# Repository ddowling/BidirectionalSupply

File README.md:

This is a design for a Bidirectional Buck-Boost DC-DC converter based on the Texas Instruments [BQ25758](https://www.ti.com/lit/ds/symlink/bq25758.pdf) integrated circuit. 
The BQ25758 has a wide supply range from 4.2V to 60V and the external MOSFETs and Inductor should support currents up to 10A. This design is closely based on the 
[BQ25758 Evaluation Module](https://www.ti.com/lit/ug/sluucd0b/sluucd0b.pdf?ts=1762398106820&ref_url=https%253A%252F%252Fwww.ti.com%252Ftool%252FBQ25758EVM). I decided to spin my own board as I
wanted to add a microcontroller and four Ideal Diodes with load switches to make a completely standalone board. 

I am interested in using this circuit as a DC UPS, Battery Charger and Solar MPPT. I have used various purpose build modules previously but I have often run into limitations due to their fixed 
function design and closed firmware.

The BQ25758 I<sub>2</sub>C interface is connected to an on-board RP2350 and there are 4 Ideal-Diode switches also connected to the RB2350. All of the high current connections are brought out to
pluggable terminal blocks so it is possible to reconfigure the circuit to accomodate different use cases. 
Having the ability to switch the DC-DC converter direction means that the system bus voltage can be decoupled from the battery voltage.

I was originally going to use a STM32 for the board microcontroller as I have used these on a lot of previous designed but when I started looking at battery capacity tracking algorithms I noted
that the more advanced employed an Unsented Kalman Filter and required the use of an Equivalent Circuit Model for the battery. I decided to opt for the
[RP2350](https://pip-assets.raspberrypi.com/categories/1214-rp2350/documents/RP-008373-DS-2-rp2350-datasheet.pdf?disposition=inline) with its hardware floating point and
the ability to run MicroPython as I figure this will be easier to iterate the firmware and run experiments on the board. Using MicroPython allow writing log files to the flash memory to
allow continous logging of battery voltage, current and temperature. This data can then be processed either on the board or remotely to allow a battery model to be fitted to actual
battery performance.

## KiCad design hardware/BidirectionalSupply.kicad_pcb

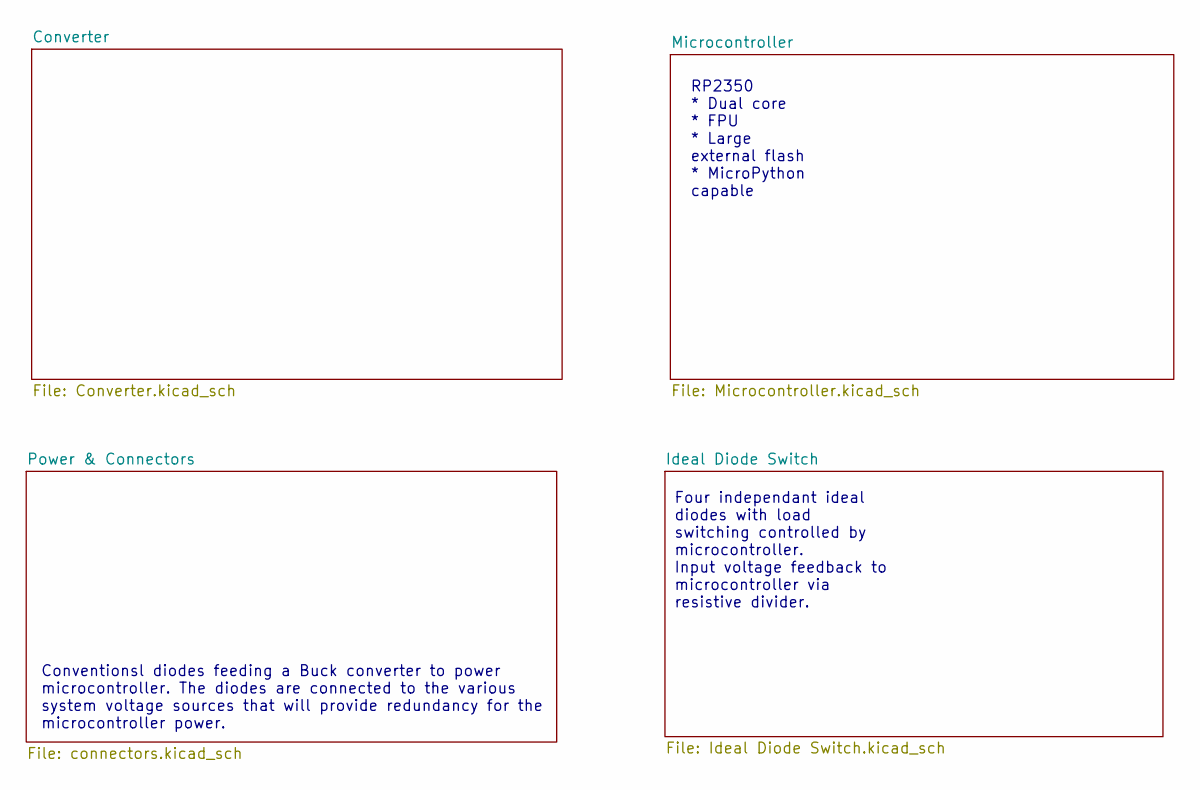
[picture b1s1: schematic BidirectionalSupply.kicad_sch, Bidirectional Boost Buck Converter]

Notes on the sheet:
RP2350 * Dual core * FPU * Large external flash * MicroPython capable
Four independant ideal diodes with load switching controlled by microcontroller. Input voltage feedback to microcontroller via resistive divider.
Conventionsl diodes feeding a Buck converter to power microcontroller. The diodes are connected to the various system voltage sources that will provide redundancy for the microcontroller power.

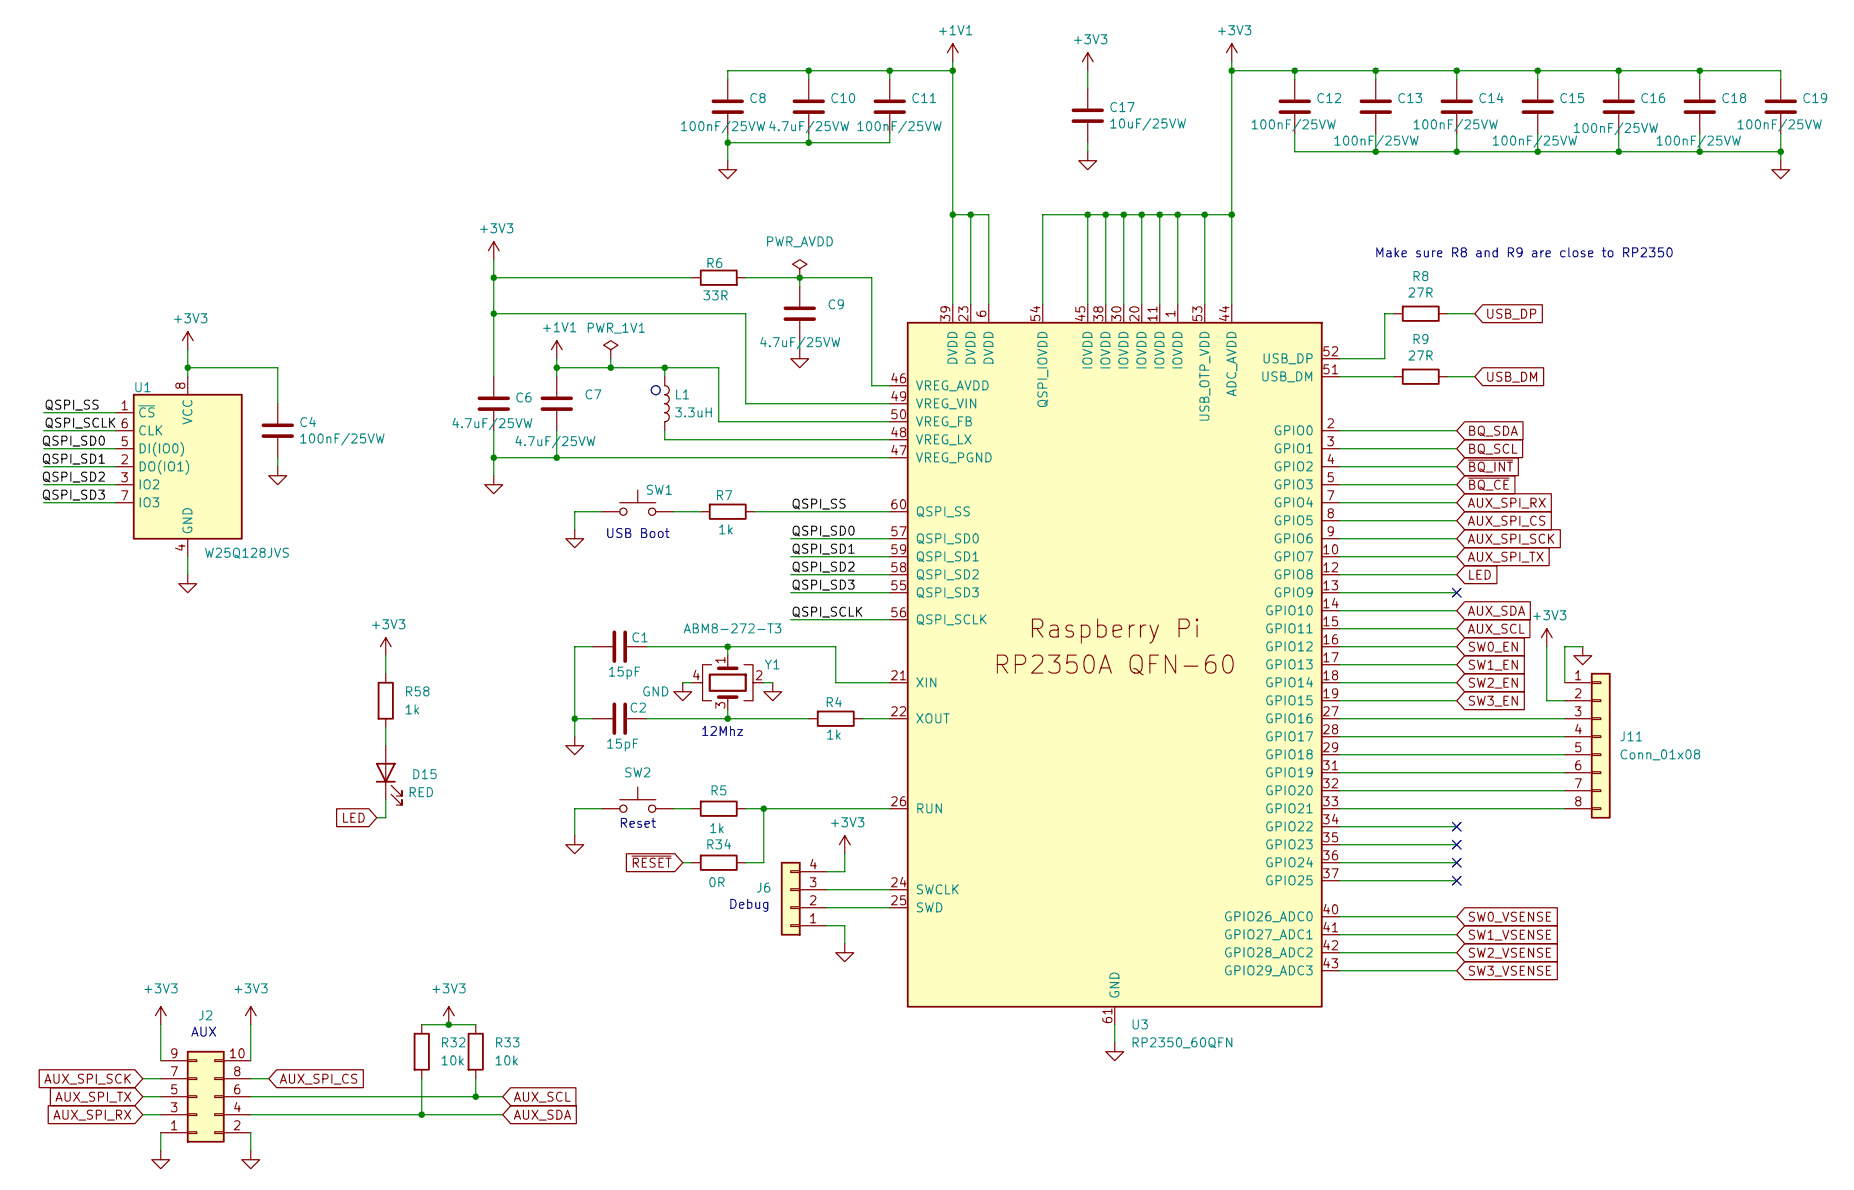
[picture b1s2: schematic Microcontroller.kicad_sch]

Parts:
C1, C2: 15pF; C_0402_DRC; JLCPCB C1548
C4, C8, C11, C12, C13, C14, C15, C16, C18, C19: 100nF/25VW; C_0603_1608Metric; JLCPCB C1590
C6, C7, C9, C10: 4.7uF/25VW; C_0805_2012Metric; JLCPCB C1779
C17: 10uF/25VW; C_0805_2012Metric; JLCPCB C15850
D15: RED; LED_0603_1608Metric; JLCPCB C2286
J2: CON10; PinHeader_2x05_P2.54mm_Vertical
J6: CON4; PinHeader_1x04_P2.54mm_Vertical
J11: Conn_01x08; PinHeader_1x08_P2.54mm_Vertical
L1: 3.3uH; L_pol_2016; JLCPCB C42411119
R4, R5, R7, R58: 1k; R_0603_1608Metric; JLCPCB C21190
R6: 33R; R_0603_1608Metric; JLCPCB C23140
R8, R9: 27R; R_0603_1608Metric; JLCPCB C25190
R32, R33: 10k; R_0603_1608Metric; JLCPCB C25804
R34: 0R; R_0603_1608Metric; JLCPCB C21189
SW1, SW2: SW_Push; TS-1088-AR02016; JLCPCB C720477
U1: W25Q128JVS; SOIC-8_5.23x5.23mm_P1.27mm; JLCPCB C97521
U3: RP2350_60QFN; RP2350-QFN-60-1EP_7x7_P0.4mm_EP3.4x3.4mm_ThermalVias; JLCPCB C42411118
Y1: ABM8-272-T3; Crystal_SMD_3225-4Pin_DRC; JLCPCB C20625731

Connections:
+1V1: C7.1, C8.1, C10.1, C11.1, L1.1, U3.6 (DVDD), U3.23 (DVDD), U3.39 (DVDD), U3.50 (VREG_FB)
+3V3: C4.1, C6.1, C12.1, C13.1, C14.1, C15.1, C16.1, C17.1, C18.1, C19.1, J2.9, J2.10, J6.4, J11.2, R6.1, R32.1, R33.1, R58.1, U1.8 (VCC), U3.1 (IOVDD), U3.11 (IOVDD), U3.20 (IOVDD), U3.30 (IOVDD), U3.38 (IOVDD), U3.44 (ADC_AVDD), U3.45 (IOVDD), U3.49 (VREG_VIN), U3.53 (USB_OTP_VDD), U3.54 (QSPI_IOVDD); also elsewhere on the board
/Microcontroller/QSPI_SCLK: U1.6 (CLK), U3.56 (QSPI_SCLK)
/Microcontroller/QSPI_SD0: U1.5 (DI(IO0)), U3.57 (QSPI_SD0)
/Microcontroller/QSPI_SD1: U1.2 (DO(IO1)), U3.59 (QSPI_SD1)
/Microcontroller/QSPI_SD2: U1.3 (IO2), U3.58 (QSPI_SD2)
/Microcontroller/QSPI_SD3: U1.7 (IO3), U3.55 (QSPI_SD3)
/Microcontroller/QSPI_SS: R7.1, U1.1 (~CS), U3.60 (QSPI_SS)
AUX_SCL: J2.6, R33.2, U3.15 (GPIO11)
AUX_SDA: J2.4, R32.2, U3.14 (GPIO10)
AUX_SPI_CS: J2.8, U3.8 (GPIO5)
AUX_SPI_RX: J2.3, U3.7 (GPIO4)
AUX_SPI_SCK: J2.7, U3.9 (GPIO6)
AUX_SPI_TX: J2.5, U3.10 (GPIO7)
BQ_SCL: U3.3 (GPIO1); also elsewhere on the board
BQ_SDA: U3.2 (GPIO0); also elsewhere on the board
GND: C1.2, C2.2, C4.2, C6.2, C7.2, C8.2, C9.2, C10.2, C11.2, C12.2, C13.2, C14.2, C15.2, C16.2, C17.2, C18.2, C19.2, J2.1, J2.2, J6.1, J11.1, SW1.1, SW2.1, U1.4 (GND), U3.47 (VREG_PGND), U3.61 (GND), Y1.2, Y1.4; also elsewhere on the board
LED: D15.1 (K), U3.12 (GPIO8)
unnamed: C2.1, R4.2, Y1.3
unnamed: D15.2 (A), R58.2
unnamed: J6.2, U3.25 (SWD)
unnamed: J6.3, U3.24 (SWCLK)
unnamed: J11.3, U3.27 (GPIO16)
unnamed: J11.4, U3.28 (GPIO17)
unnamed: J11.5, U3.29 (GPIO18)
unnamed: J11.6, U3.31 (GPIO19)
unnamed: J11.7, U3.32 (GPIO20)
unnamed: J11.8, U3.33 (GPIO21)
unnamed: R5.2, SW2.2
unnamed: R7.2, SW1.2
unnamed: R5.1, R34.1, U3.26 (RUN)
unnamed: R9.2, U3.51 (USB_DM)
unnamed: R8.2, U3.52 (USB_DP)
unnamed: C9.1, R6.2, U3.46 (VREG_AVDD)
unnamed: L1.2, U3.48 (VREG_LX)
unnamed: C1.1, U3.21 (XIN), Y1.1
unnamed: R4.1, U3.22 (XOUT)
SW0_EN: U3.16 (GPIO12); also elsewhere on the board
SW0_VSENSE: U3.40 (GPIO26_ADC0); also elsewhere on the board
SW1_EN: U3.17 (GPIO13); also elsewhere on the board
SW1_VSENSE: U3.41 (GPIO27_ADC1); also elsewhere on the board
SW2_EN: U3.18 (GPIO14); also elsewhere on the board
SW2_VSENSE: U3.42 (GPIO28_ADC2); also elsewhere on the board
SW3_EN: U3.19 (GPIO15); also elsewhere on the board
SW3_VSENSE: U3.43 (GPIO29_ADC3); also elsewhere on the board
USB_DM: R9.1; also elsewhere on the board
USB_DP: R8.1; also elsewhere on the board
~BQ_CE: U3.5 (GPIO3); also elsewhere on the board
~BQ_INT: U3.4 (GPIO2); also elsewhere on the board
~RESET: R34.2; also elsewhere on the board

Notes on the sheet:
Debug
Make sure R8 and R9 are close to RP2350
USB Boot
AUX
Reset
12Mhz

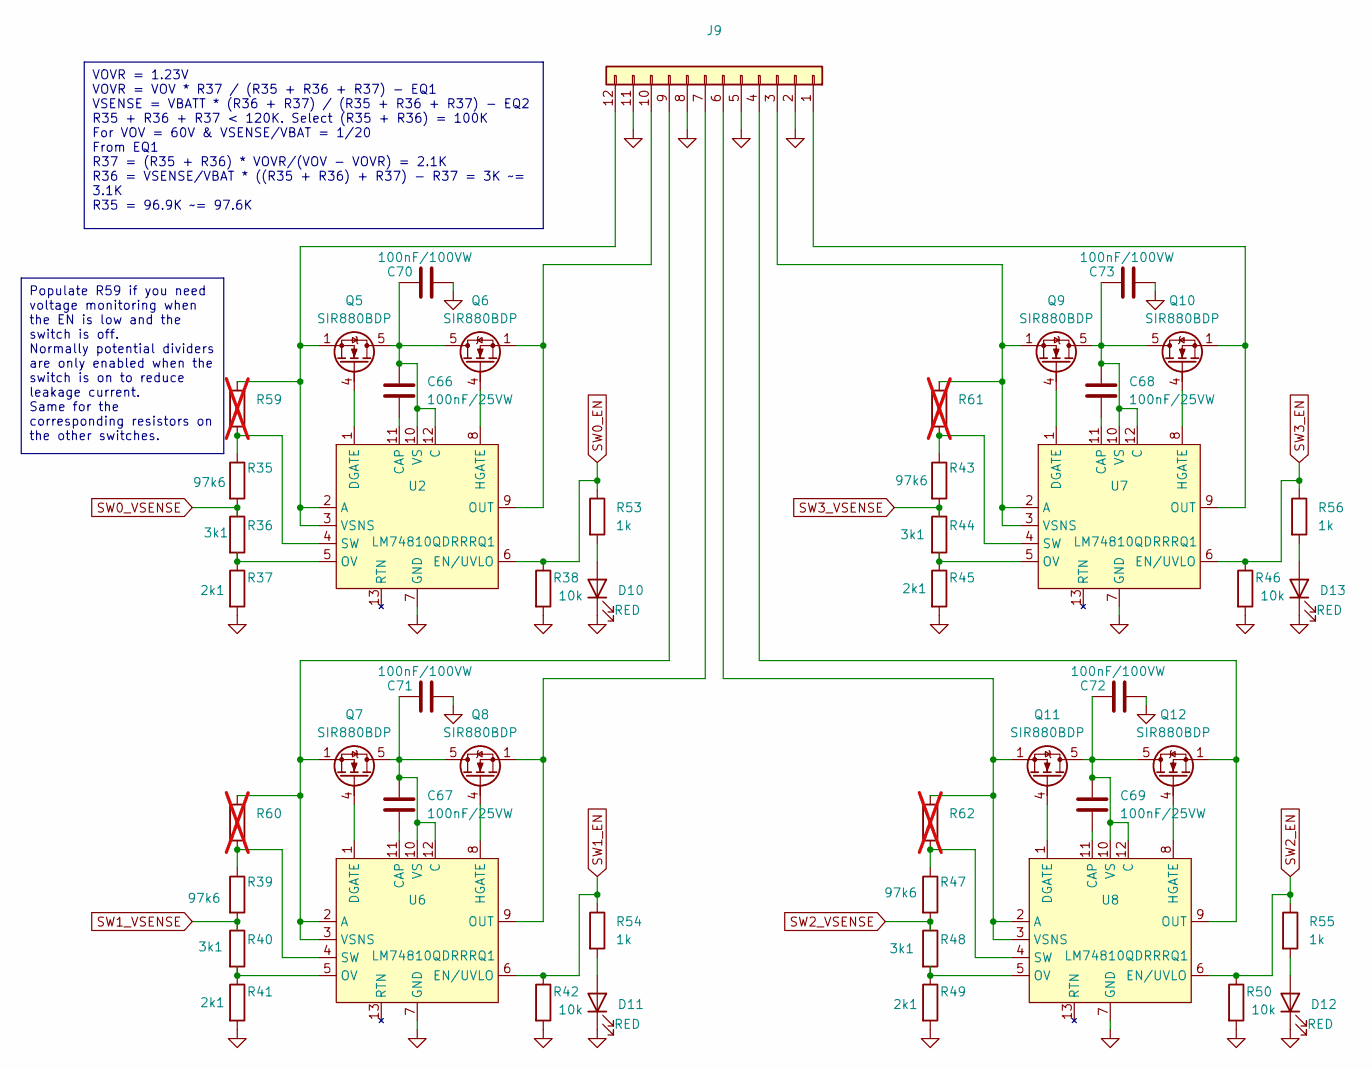
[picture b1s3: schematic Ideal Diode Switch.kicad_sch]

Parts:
C66, C67, C68, C69: 100nF/25VW; C_0603_1608Metric; JLCPCB C1590
C70, C71, C72, C73: 100nF/100VW; C_1206_3216Metric; JLCPCB C1945
D10, D11, D12, D13: RED; LED_0603_1608Metric; JLCPCB C2286
J9: Conn_01x12; PhoenixContact_MSTBVA_2,5_12-G-5,08_1x12_P5.08mm_Vertical; Mouser 651-1755833
Q5, Q6, Q7, Q8, Q9, Q10, Q11, Q12: SIR880BDP; POWERPAK-SO-8_L6.2-W5.2-P1.27-BL-EP; LCSC Part C5900133
R35, R39, R43, R47: 97k6; R_0603_1608Metric; JLCPCB C2907079
R36, R40, R44, R48: 3k1; R_0603_1608Metric; JLCPCB C2924132
R37, R41, R45, R49: 2k1; R_0603_1608Metric; JLCPCB C22902
R38, R42, R46, R50: 10k; R_0603_1608Metric; JLCPCB C25804
R53, R54, R55, R56: 1k; R_0603_1608Metric; JLCPCB C21190
R59, R60, R61, R62: 0R; R_0603_1608Metric; not fitted
U2, U6, U7, U8: LM74810QDRRRQ1; WSON-12_L3.0-W3.0-P0.50-TL-EP-2; LCSC Part C3215601

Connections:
GND: C70.2, C71.2, C72.2, C73.2, D10.1 (K), D11.1 (K), D12.1 (K), D13.1 (K), J9.2, J9.5, J9.8, J9.11, R37.2, R38.2, R41.2, R42.2, R45.2, R46.2, R49.2, R50.2, U2.7 (GND), U6.7 (GND), U7.7 (GND), U8.7 (GND); also elsewhere on the board
unnamed: D10.2 (A), R53.2
unnamed: D11.2 (A), R54.2
unnamed: D12.2 (A), R55.2
unnamed: D13.2 (A), R56.2
unnamed: J9.1, Q10.1 (S), Q10.2 (S), Q10.3 (S), U7.9 (OUT)
unnamed: J9.3, Q9.1 (S), Q9.2 (S), Q9.3 (S), R61.1, U7.2 (A), U7.3 (VSNS)
unnamed: J9.4, Q12.1 (S), Q12.2 (S), Q12.3 (S), U8.9 (OUT)
unnamed: J9.6, Q11.1 (S), Q11.2 (S), Q11.3 (S), R62.1, U8.2 (A), U8.3 (VSNS)
unnamed: J9.7, Q8.1 (S), Q8.2 (S), Q8.3 (S), U6.9 (OUT)
unnamed: J9.9, Q7.1 (S), Q7.2 (S), Q7.3 (S), R60.1, U6.2 (A), U6.3 (VSNS)
unnamed: J9.10, Q6.1 (S), Q6.2 (S), Q6.3 (S), U2.9 (OUT)
unnamed: J9.12, Q5.1 (S), Q5.2 (S), Q5.3 (S), R59.1, U2.2 (A), U2.3 (VSNS)
unnamed: C66.1, C70.1, Q5.5 (D), Q5.6 (D), Q5.7 (D), Q5.8 (D), Q5.9 (EP), Q6.5 (D), Q6.6 (D), Q6.7 (D), Q6.8 (D), Q6.9 (EP), U2.10 (VS), U2.12 (C)
unnamed: Q5.4 (G), U2.1 (DGATE)
unnamed: Q6.4 (G), U2.8 (HGATE)
unnamed: C67.1, C71.1, Q7.5 (D), Q7.6 (D), Q7.7 (D), Q7.8 (D), Q7.9 (EP), Q8.5 (D), Q8.6 (D), Q8.7 (D), Q8.8 (D), Q8.9 (EP), U6.10 (VS), U6.12 (C)
unnamed: Q7.4 (G), U6.1 (DGATE)
unnamed: Q8.4 (G), U6.8 (HGATE)
unnamed: Q9.4 (G), U7.1 (DGATE)
unnamed: C68.1, C73.1, Q9.5 (D), Q9.6 (D), Q9.7 (D), Q9.8 (D), Q9.9 (EP), Q10.5 (D), Q10.6 (D), Q10.7 (D), Q10.8 (D), Q10.9 (EP), U7.10 (VS), U7.12 (C)
unnamed: Q10.4 (G), U7.8 (HGATE)
unnamed: C69.1, C72.1, Q11.5 (D), Q11.6 (D), Q11.7 (D), Q11.8 (D), Q11.9 (EP), Q12.5 (D), Q12.6 (D), Q12.7 (D), Q12.8 (D), Q12.9 (EP), U8.10 (VS), U8.12 (C)
unnamed: Q11.4 (G), U8.1 (DGATE)
unnamed: Q12.4 (G), U8.8 (HGATE)
unnamed: C66.2, U2.11 (CAP)
unnamed: R36.2, R37.1, U2.5 (OV)
unnamed: R35.1, R59.2, U2.4 (SW)
unnamed: C67.2, U6.11 (CAP)
unnamed: R40.2, R41.1, U6.5 (OV)
unnamed: R39.1, R60.2, U6.4 (SW)
unnamed: C68.2, U7.11 (CAP)
unnamed: R44.2, R45.1, U7.5 (OV)
unnamed: R43.1, R61.2, U7.4 (SW)
unnamed: C69.2, U8.11 (CAP)
unnamed: R48.2, R49.1, U8.5 (OV)
unnamed: R47.1, R62.2, U8.4 (SW)
SW0_EN: R38.1, R53.1, U2.6 (EN/UVLO); also elsewhere on the board
SW0_VSENSE: R35.2, R36.1; also elsewhere on the board
SW1_EN: R42.1, R54.1, U6.6 (EN/UVLO); also elsewhere on the board
SW1_VSENSE: R39.2, R40.1; also elsewhere on the board
SW2_EN: R50.1, R55.1, U8.6 (EN/UVLO); also elsewhere on the board
SW2_VSENSE: R47.2, R48.1; also elsewhere on the board
SW3_EN: R46.1, R56.1, U7.6 (EN/UVLO); also elsewhere on the board
SW3_VSENSE: R43.2, R44.1; also elsewhere on the board

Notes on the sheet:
VOVR = 1.23V VOVR = VOV * R37 / (R35 + R36 + R37) - EQ1 VSENSE = VBATT * (R36 + R37) / (R35 + R36 + R37) - EQ2 R35 + R36 + R37 < 120K. Select (R35 + R36) = 100K For VOV = 60V & VSENSE/VBAT = 1/20 From EQ1 R37 = (R35 + R36) * VOVR/(VOV - VOVR) = 2.1K R36 = VSENSE/VBAT * ((R35 + R36) + R37) - R37 = 3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
Populate R59 if you need voltage monitoring when the EN is low and the switch is off. Normally potential dividers are only enabled when the switch is on to reduce leakage current. Same for the corresponding resistors on the other switches.

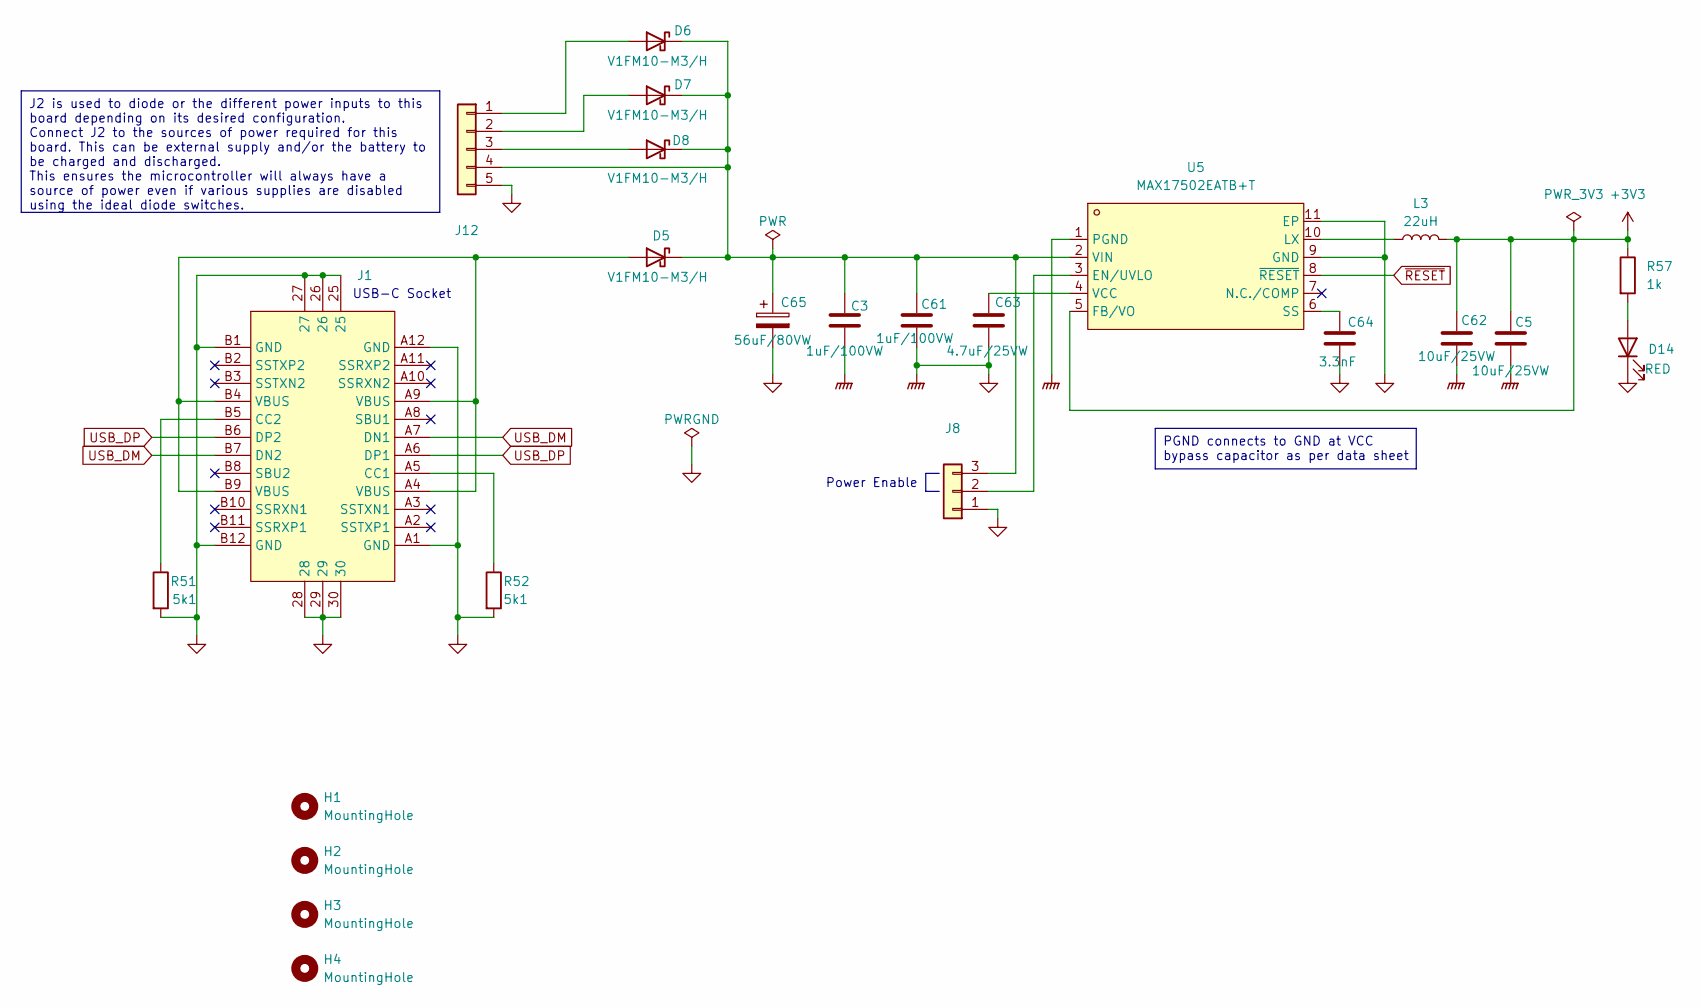
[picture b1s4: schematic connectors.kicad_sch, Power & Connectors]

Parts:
C3, C61: 1uF/100VW; C_1206_3216Metric; JLCPCB C13832
C5, C62: 10uF/25VW; C_0805_2012Metric; JLCPCB C15850
C63: 4.7uF/25VW; C_0805_2012Metric; JLCPCB C1779
C64: 3.3nF; C_0603_1608Metric; JLCPCB C1613
C65: 56uF/80VW; CP_Elec_10x10.5; JLCPCB C128515
D5, D6, D7, D8: V1FM10-M3/H; D_SMF; JLCPCB C3758930
D14: RED; LED_0603_1608Metric; JLCPCB C2286
H1, H2, H3, H4: MountingHole; MountingHole_3.2mm_M3_Pad
J1: USB-309GC-B-SU; USB-C-SMD_USB-309GC-B-SU; LCSC Part C309336
J8: Conn_01x03; PinHeader_1x03_P2.54mm_Vertical
J12: Conn_01x05; PhoenixContact_MSTBVA_2,5_5-G-5,08_1x05_P5.08mm_Vertical
L3: 22uH; IND-SMD_L4.0-W4.0_SLW4010S; JLCPCB C83472
R51, R52: 5k1; R_0603_1608Metric; JLCPCB C23186
R57: 1k; R_0603_1608Metric; JLCPCB C21190
U5: MAX17502EATB+T; DFN-10_L3.0-W2.0-P0.50-BL-EP; LCSC Part C571005

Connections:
+3V3: C5.1, C62.1, L3.2, R57.1, U5.5 (FB/VO); also elsewhere on the board
GND: C3.2, C5.2, C61.2, C62.2, C63.2, C64.2, C65.2, D14.1 (K), J1.25, J1.26, J1.27, J1.28, J1.29, J1.30, J1.A1 (GND), J1.A12 (GND), J1.B1 (GND), J1.B12 (GND), J8.1, J12.5, R51.2, R52.2, U5.1 (PGND), U5.9 (GND), U5.11 (EP); also elsewhere on the board
unnamed: D5.2 (A), J1.A4 (VBUS), J1.A9 (VBUS), J1.B4 (VBUS), J1.B9 (VBUS)
unnamed: C3.1, C61.1, C65.1, D5.1 (K), D6.1 (K), D7.1 (K), D8.1 (K), J8.3, J12.4, U5.2 (VIN)
unnamed: D6.2 (A), J12.1
unnamed: D7.2 (A), J12.2
unnamed: D8.2 (A), J12.3
unnamed: D14.2 (A), R57.2
unnamed: J1.A5 (CC1), R52.1
unnamed: J1.B5 (CC2), R51.1
unnamed: J8.2, U5.3 (EN/UVLO)
unnamed: L3.1, U5.10 (LX)
unnamed: C64.1, U5.6 (SS)
unnamed: C63.1, U5.4 (VCC)
USB_DM: J1.A7 (DN1), J1.B7 (DN2); also elsewhere on the board
USB_DP: J1.A6 (DP1), J1.B6 (DP2); also elsewhere on the board
~RESET: U5.8 (~RESET); also elsewhere on the board

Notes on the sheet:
PGND connects to GND at VCC bypass capacitor as per data sheet
J2 is used to diode or the different power inputs to this board depending on its desired configuration. Connect J2 to the sources of power required for this board. This can be external supply and/or the battery to be charged and discharged. This ensures the microcontroller will always have a source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
USB-C Socket
Power Enable

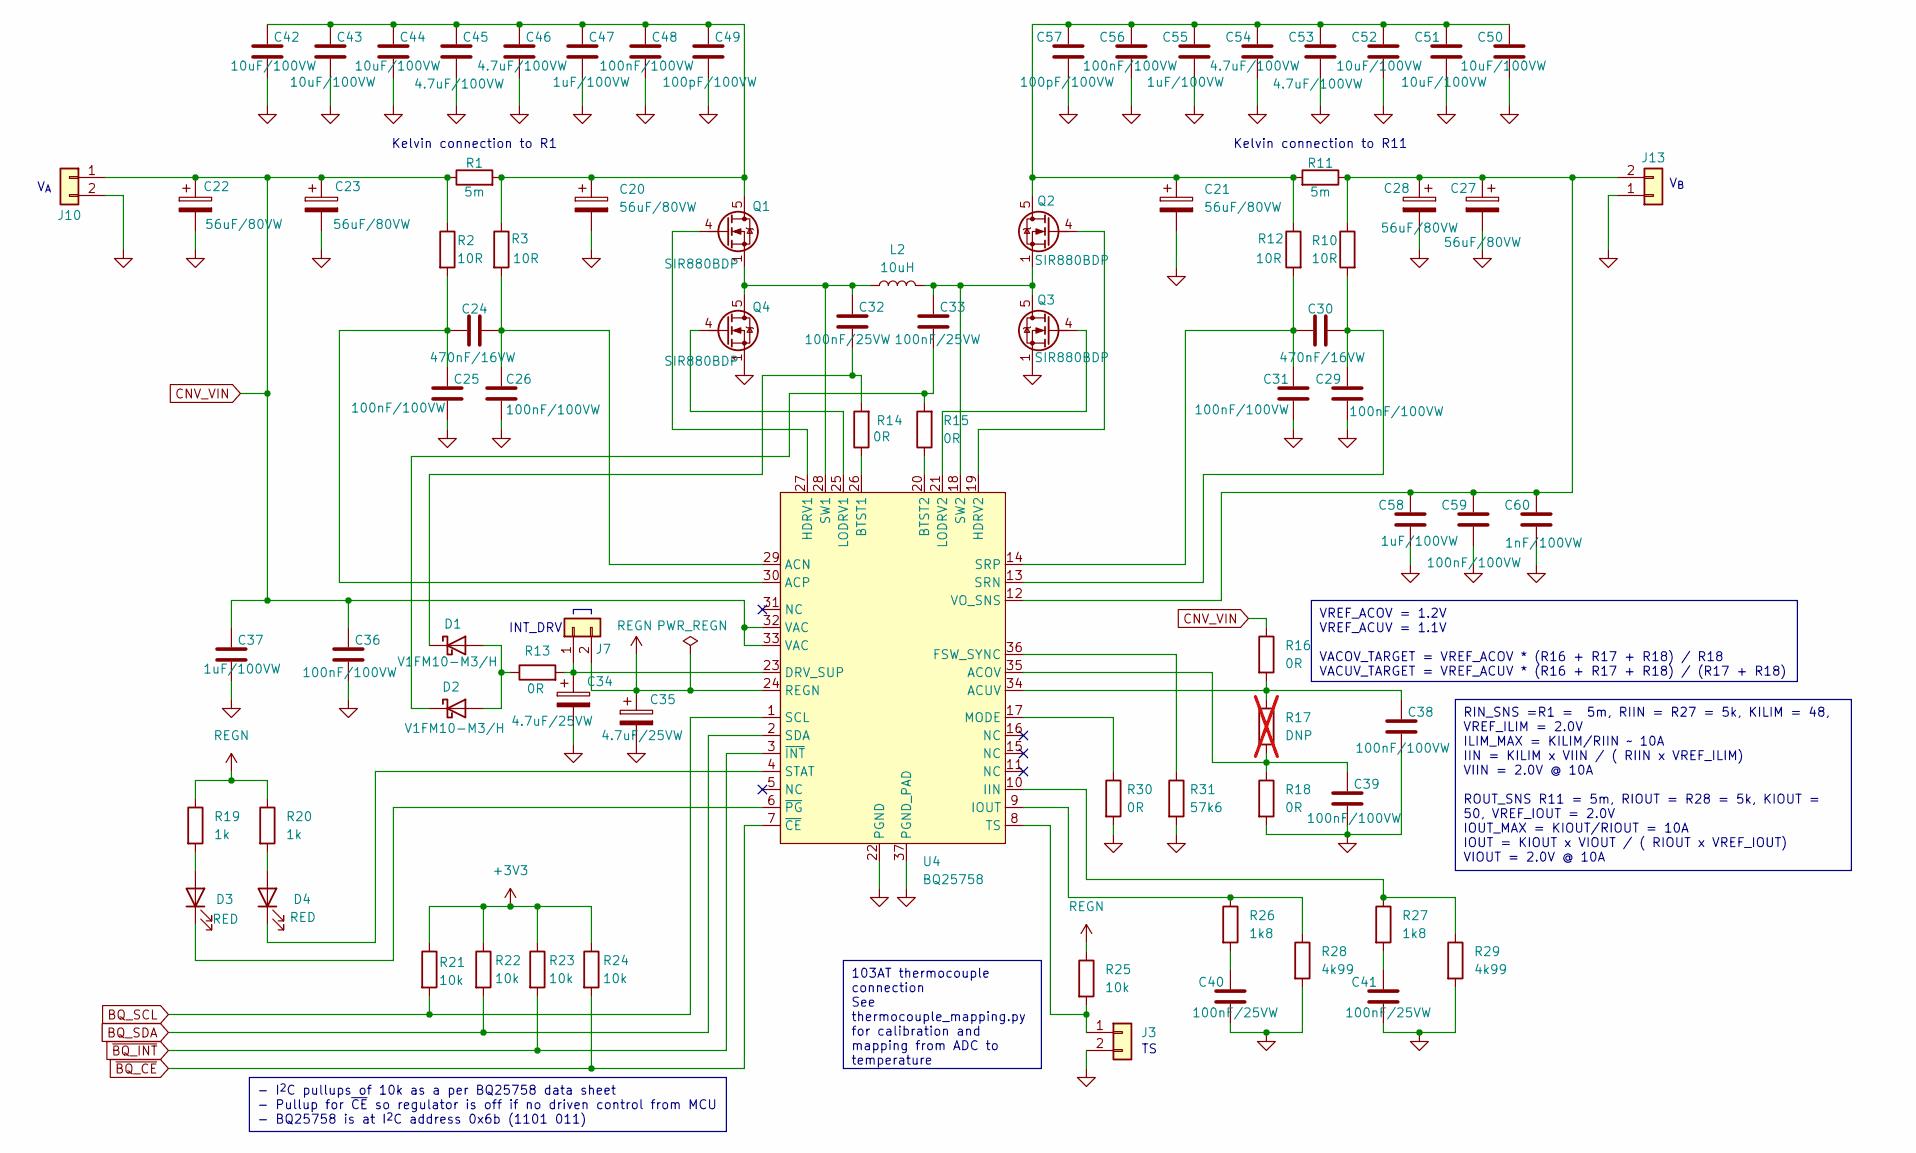
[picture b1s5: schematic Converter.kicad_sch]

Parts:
C20, C21, C22, C23, C27, C28: 56uF/80VW; CP_Elec_10x10.5; JLCPCB C128515
C24, C30: 470nF/16VW; C_0603_1608Metric; JLCPCB C1623
C25, C26, C29, C31, C36, C38, C39, C48, C56, C59: 100nF/100VW; C_1206_3216Metric; JLCPCB C1945
C32, C33, C40, C41: 100nF/25VW; C_0603_1608Metric; JLCPCB C1590
C34, C35: 4.7uF/25VW; C_0805_2012Metric; JLCPCB C1779
C37, C47, C55, C58: 1uF/100VW; C_1206_3216Metric; JLCPCB C13832
C42, C43, C44, C50, C51, C52: 10uF/100VW; C_1210_3225Metric; JLCPCB C5156756
C45, C46, C53, C54: 4.7uF/100VW; C_1210_3225Metric; JLCPCB C385986
C49, C57: 100pF/100VW; C_0805_2012Metric; JLCPCB C37456
C60: 1nF/100VW; C_0805_2012Metric; JLCPCB C15177
D1, D2: V1FM10-M3/H; D_SMF; JLCPCB C3758930
D3, D4: RED; LED_0603_1608Metric; JLCPCB C2286
J3, J7: CON2; PinHeader_1x02_P2.54mm_Vertical
J10, J13: Conn_01x02; PhoenixContact_MSTBVA_2,5_2-G-5,08_1x02_P5.08mm_Vertical
L2: 10uH; L_Wuerth_HCM-1350; Mouser 530-SCIHP1367-100M
Q1, Q2, Q3, Q4: SIR880BDP; POWERPAK-SO-8_L6.2-W5.2-P1.27-BL-EP; LCSC Part C5900133
R1, R11: 5m; RES-SMD_L10.0-W5.2; JLCPCB C481477
R2, R3, R10, R12: 10R; R_0603_1608Metric; JLCPCB C22859
R13, R14, R15, R16, R18, R30: 0R; R_0603_1608Metric; JLCPCB C21189
R17: DNP; R_0603_1608Metric; not fitted
R19, R20: 1k; R_0603_1608Metric; JLCPCB C21190
R21, R22, R23, R24, R25: 10k; R_0603_1608Metric; JLCPCB C25804
R26, R27: 1k8; R_0603_1608Metric; JLCPCB C4177
R28, R29: 4k99; R_0603_1608Metric; JLCPCB C2692815
R31: 57k6; R_0603_1608Metric; JLCPCB C23082
U4: BQ25758; QFN-36_L6.0-W5.0-P0.50-BL-EP-1; JLCPCB C33222334

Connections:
+3V3: R21.1, R22.1, R23.1, R24.1; also elsewhere on the board
BQ_SCL: R21.2, U4.1 (SCL); also elsewhere on the board
BQ_SDA: R22.2, U4.2 (SDA); also elsewhere on the board
CNV_VIN: C22.1, C23.1, C36.1, C37.1, J10.1, R1.1, R2.1, R16.1, U4.32 (VAC), U4.33 (VAC)
GND: C20.2, C21.2, C22.2, C23.2, C25.2, C26.2, C27.2, C28.2, C29.2, C31.2, C34.2, C35.2, C36.2, C37.2, C38.2, C39.2, C40.2, C41.2, C42.2, C43.2, C44.2, C45.2, C46.2, C47.2, C48.2, C49.2, C50.2, C51.2, C52.2, C53.2, C54.2, C55.2, C56.2, C57.2, C58.2, C59.2, C60.2, J3.2, J10.2, J13.1, Q3.1 (S), Q3.2 (S), Q3.3 (S), Q4.1 (S), Q4.2 (S), Q4.3 (S), R18.2, R28.2, R29.2, R30.2, R31.2, U4.22 (PGND), U4.37 (PGND_PAD); also elsewhere on the board
unnamed: C40.1, R26.2
unnamed: C41.1, R27.2
unnamed: D1.2 (A), D2.2 (A), R13.1
unnamed: C32.2, D1.1 (K), R14.2
unnamed: C33.2, D2.1 (K), R15.2
unnamed: D3.2 (A), R19.2
unnamed: D3.1 (K), U4.6 (~PG)
unnamed: D4.2 (A), R20.2
unnamed: D4.1 (K), U4.4 (STAT)
unnamed: J3.1, R25.2, U4.8 (TS)
unnamed: C34.1, J7.1, R13.2, U4.23 (DRV_SUP)
unnamed: C27.1, C28.1, C58.1, C59.1, C60.1, J13.2, R10.1, R11.1, U4.12 (VO_SNS)
unnamed: C20.1, C42.1, C43.1, C44.1, C45.1, C46.1, C47.1, C48.1, C49.1, Q1.5 (D), Q1.6 (D), Q1.7 (D), Q1.8 (D), Q1.9 (EP), R1.2, R3.1
unnamed: Q1.4 (G), U4.27 (HDRV1)
unnamed: C21.1, C50.1, C51.1, C52.1, C53.1, C54.1, C55.1, C56.1, C57.1, Q2.5 (D), Q2.6 (D), Q2.7 (D), Q2.8 (D), Q2.9 (EP), R11.2, R12.1
unnamed: Q2.4 (G), U4.19 (HDRV2)
unnamed: C33.1, L2.2, Q2.1 (S), Q2.2 (S), Q2.3 (S), Q3.5 (D), Q3.6 (D), Q3.7 (D), Q3.8 (D), Q3.9 (EP), U4.18 (SW2)
unnamed: Q3.4 (G), U4.21 (LODRV2)
unnamed: C32.1, L2.1, Q1.1 (S), Q1.2 (S), Q1.3 (S), Q4.5 (D), Q4.6 (D), Q4.7 (D), Q4.8 (D), Q4.9 (EP), U4.28 (SW1)
unnamed: Q4.4 (G), U4.25 (LODRV1)
unnamed: C24.2, C26.1, R3.2, U4.29 (ACN)
unnamed: C39.1, R17.2, R18.1, U4.35 (ACOV)
unnamed: C24.1, C25.1, R2.2, U4.30 (ACP)
unnamed: C38.1, R16.2, R17.1, U4.34 (ACUV)
unnamed: R14.1, U4.26 (BTST1)
unnamed: R15.1, U4.20 (BTST2)
unnamed: R31.1, U4.36 (FSW_SYNC)
unnamed: R27.1, R29.1, U4.10 (IIN)
unnamed: R26.1, R28.1, U4.9 (IOUT)
unnamed: R30.1, U4.17 (MODE)
unnamed: C29.1, C30.1, R10.2, U4.13 (SRN)
unnamed: C30.2, C31.1, R12.2, U4.14 (SRP)
REGN: C35.1, J7.2, R19.1, R20.1, R25.1, U4.24 (REGN)
~BQ_CE: R24.2, U4.7 (~CE); also elsewhere on the board
~BQ_INT: R23.2, U4.3 (~INT); also elsewhere on the board

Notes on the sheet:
103AT thermocouple connection See thermocouple_mapping.py for calibration and mapping from ADC to temperature
RIN_SNS =R1 = 5m, RIIN = R27 = 5k, KILIM = 48, VREF_ILIM = 2.0V ILIM_MAX = KILIM/RIIN ~ 10A IIN = KILIM x VIIN / ( RIIN x VREF_ILIM) VIIN = 2.0V @ 10A ROUT_SNS R11 = 5m, RIOUT = R28 = 5k, KIOUT = 50, VREF_IOUT = 2.0V IOUT_MAX = KIOUT/RIOUT = 10A IOUT = KIOUT x VIOUT / ( RIOUT x VREF_IOUT) VIOUT = 2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
VREF_ACOV = 1.2V VREF_ACUV = 1.1V VACOV_TARGET = VREF_ACOV * (R16 + R17 + R18) / R18 VACUV_TARGET = VREF_ACUV * (R16 + R17 + R18) / (R17 + R18)
- I^{2}C pullups of 10k as a per BQ25758 data sheet - Pullup for ~{CE} so regulator is off if no driven control from MCU - BQ25758 is at I^{2}C address 0x6b (1101 011)
Kelvin connection to R11
V_{A}
V_{B}
INT_DRV
Kelvin connection to R1

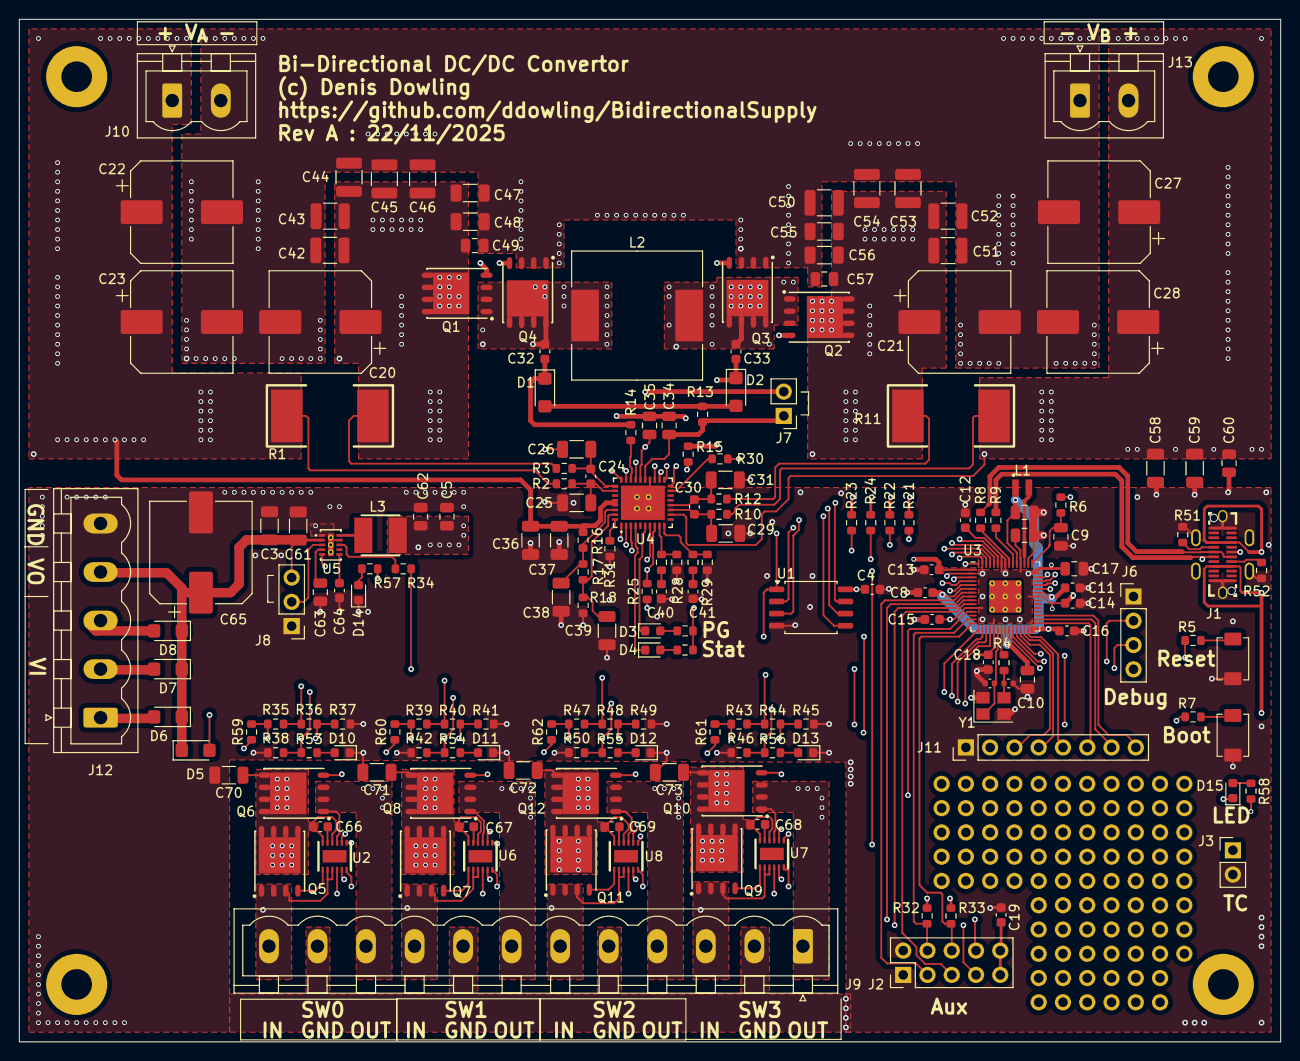
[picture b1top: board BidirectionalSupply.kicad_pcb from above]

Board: 4 copper layers, 132.0 x 107.0 mm, 190 parts (0 on the bottom side), 132 nets.

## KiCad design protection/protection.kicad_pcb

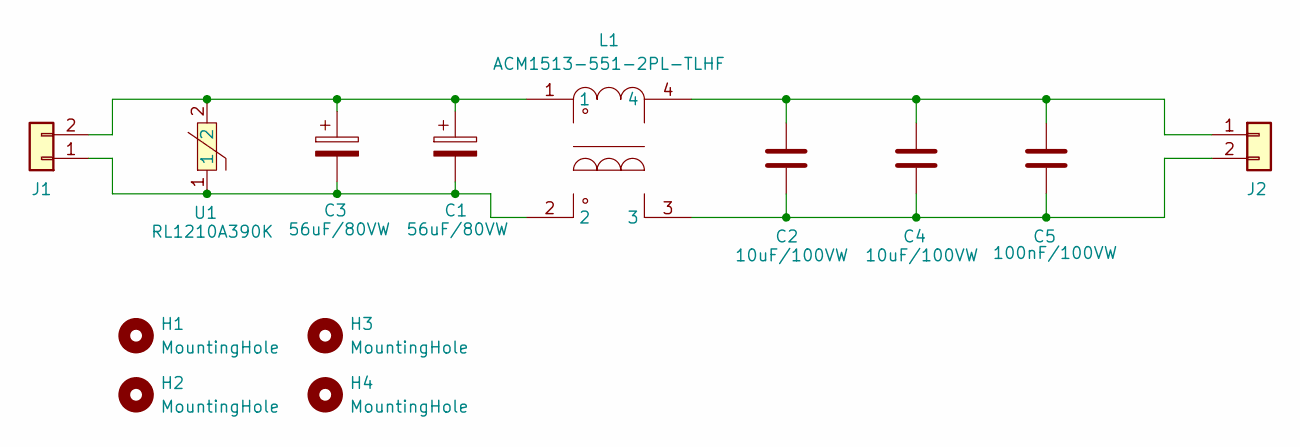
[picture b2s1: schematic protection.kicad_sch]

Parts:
C1, C3: 56uF/80VW; CP_Elec_10x10.5; LCSC Part C128515
C2, C4: 10uF/100VW; C_1210_3225Metric; LCSC Part C5156756
C5: 100nF/100VW; C_1206_3216Metric; LCSC Part C1945
H1, H2, H3, H4: MountingHole; MountingHole_3.2mm_M3_DIN965_Pad
J1, J2: Conn_01x02; PhoenixContact_MSTBVA_2,5_2-G-5,08_1x02_P5.08mm_Vertical
L1: ACM1513-551-2PL-TLHF; FILTER-SMD_4P-L15.0-W13.0-BL; LCSC Part C111471
U1: RL1210A390K; R1210; LCSC Part C19267881

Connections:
unnamed: C1.2, C3.2, J1.1, L1.2, U1.1
unnamed: C1.1, C3.1, J1.2, L1.1, U1.2
unnamed: C2.1, C4.1, C5.1, J2.1, L1.4
unnamed: C2.2, C4.2, C5.2, J2.2, L1.3

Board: 2 copper layers, 13 parts (0 on the bottom side), 4 nets, no tracks yet.

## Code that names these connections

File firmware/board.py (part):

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from calibration import Calibration
from display import display_convertor_info, display_blank, display_error

bq_sda = Pin(0)
bq_scl = Pin(1)
bq_int = Pin(2, Pin.IN)

# Inverted logic on this pin. Want output to stay high until explicitly enabled
bq_ce = Pin(3, Pin.OUT, True)

# LED on Pin(8), active-low. PWM: duty 0 = full on, 65535 = off.
_led_pwm = PWM(Pin(8, Pin.OUT), freq=100_000, duty_u16=65535)


# Ideal Diode switches
sw0_en = Pin(12, Pin.OUT)
sw1_en = Pin(13, Pin.OUT)
sw2_en = Pin(14, Pin.OUT)
sw3_en = Pin(15, Pin.OUT)
sw0_vsense = ADC(Pin(26))
sw1_vsense = ADC(Pin(27))
sw2_vsense = ADC(Pin(28))
sw3_vsense = ADC(Pin(29))

bq_i2c = I2C(0, sda=bq_sda, scl=bq_scl)

bq = BQ25758(i2c_bus=bq_i2c, chip_enable_pin=bq_ce)

# Load calibration data
calibration = Calibration()
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
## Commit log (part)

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2025-11-05 Added RP2350 reference design as I will be using these components in this application
2025-11-07 WIP checkin of schematic
2025-11-07 WIP checkin * Added most of the JLCPCB part numbers * Added most of the component footprints * Connected up microcontroller and dc/dc converter
2025-11-09 Cleaned up share library Added switchmode 3v3 supply
2025-11-11 Schematic is now mostly complete. Will review and then move onto the PCB layout
2025-11-11 Checked all DC/DC converter capacitors Some part substitution to preference in stock items
2025-11-11 Add BOM csv
2025-11-13 All components placed on board and most 3D shapes are present
2025-11-19 - Routed board with all fixable DRC errors and warnings fixed
2025-11-20 Added summary page Added prototyping area to PCB
2025-11-21 Ready for trial submit to JLCPCB
2025-11-22 * Added the JLCPCB Fabrication Plugin into KiCad and use this for the exports * Fixed problem detected with capacitor footprint for C42, C43, C44, C50, C51, C52
2025-11-24 Start of some firmware
2025-11-26 Removed the included RP2350 minimal board as should not be needed for symbols any more.
2025-11-26 Added a design for a simple MOV and common mode choke input protection circuit
2025-11-26 Update to the title block
2025-11-27 Designs as submitted on 27/11/2025
2026-02-18 Added board #4 and #5 calibration data
2026-02-25 Added some useful functions to itech_remote.py. This can now be used to query the connected ITECH load and do some simple measurements
2026-02-25 PWM control of the onboard LED
2026-02-25 whitespace clean
2026-03-04 - Original version of the st7789 display driver. I will drop this as it does not work as well as the st7789-framebuffer class
2026-03-04 Some initial work on a display driver
2026-03-04 - Code to exercise the ezFBfont class
2026-03-17 Added load_sweep.py to test the constant current mode Added indication of when the DC/DC convertor is in either CV, CC or Off mode.
2026-03-22 Added example role.dat and startup.dat. These files have embedded comments to explain the various settings they can contain.
2026-03-29 Add battery SOC estimator and capacity test tooling
    firmware/soc.py: new SocEstimator class using coulomb counting with OCV
    anchoring. Anchors from OCV table on startup (before charging begins),
    after 120s at rest, and at 100% when charge cycle completes.
    firmware/charger.py: integrate SocEstimator into BatteryCharger.
    ChargingProfile gains ocv_table field; LIFEPO4_2S_5AH includes
    approximate default OCV table. SOC ticked each update cycle with signed
2026-03-29 Fixed ordering of IT8511 connection messages

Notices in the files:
firmware/board.py:
Copyright (c) 2026 Denis Dowling (dpd@opsol.com.au)
